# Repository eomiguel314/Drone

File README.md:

<img src="https://private-user-images.githubusercontent.com/155032115/534239275-43df6516-5e8d-49b2-8379-d691b3563eec.png?jwt=eyJ0eXAiOiJKV1QiLCJhbGciOiJIUzI1NiJ9.eyJpc3MiOiJnaXRodWIuY29tIiwiYXVkIjoicmF3LmdpdGh1YnVzZXJjb250ZW50LmNvbSIsImtleSI6ImtleTUiLCJleHAiOjE3NjgwNjI2MjAsIm5iZiI6MTc2ODA2MjMyMCwicGF0aCI6Ii8xNTUwMzIxMTUvNTM0MjM5Mjc1LTQzZGY2NTE2LTVlOGQtNDliMi04Mzc5LWQ2OTFiMzU2M2VlYy5wbmc_WC1BbXotQWxnb3JpdGhtPUFXUzQtSE1BQy1TSEEyNTYmWC1BbXotQ3JlZGVudGlhbD1BS0lBVkNPRFlMU0E1M1BRSzRaQSUyRjIwMjYwMTEwJTJGdXMtZWFzdC0xJTJGczMlMkZhd3M0X3JlcXVlc3QmWC1BbXotRGF0ZT0yMDI2MDExMFQxNjI1MjBaJlgtQW16LUV4cGlyZXM9MzAwJlgtQW16LVNpZ25hdHVyZT03NzFiOGY2MzdkZTdjZjNjMDJiNzgxZWViOGYxYjNmYWFjZmI5NjM2MTRmMWU0MmQyMjM3NjM1OWRiNDJlYmY5JlgtQW16LVNpZ25lZEhlYWRlcnM9aG9zdCJ9.WQfb5ywTV8FJy9Pylw90fT3kKYA23nSvT_et_dpvcMw"/>

# What is the project?
<p>This is a quadcopter with a flight controler based on esp32 with Mpu6050 and BME280....<p/>

# PCB of the flight controller

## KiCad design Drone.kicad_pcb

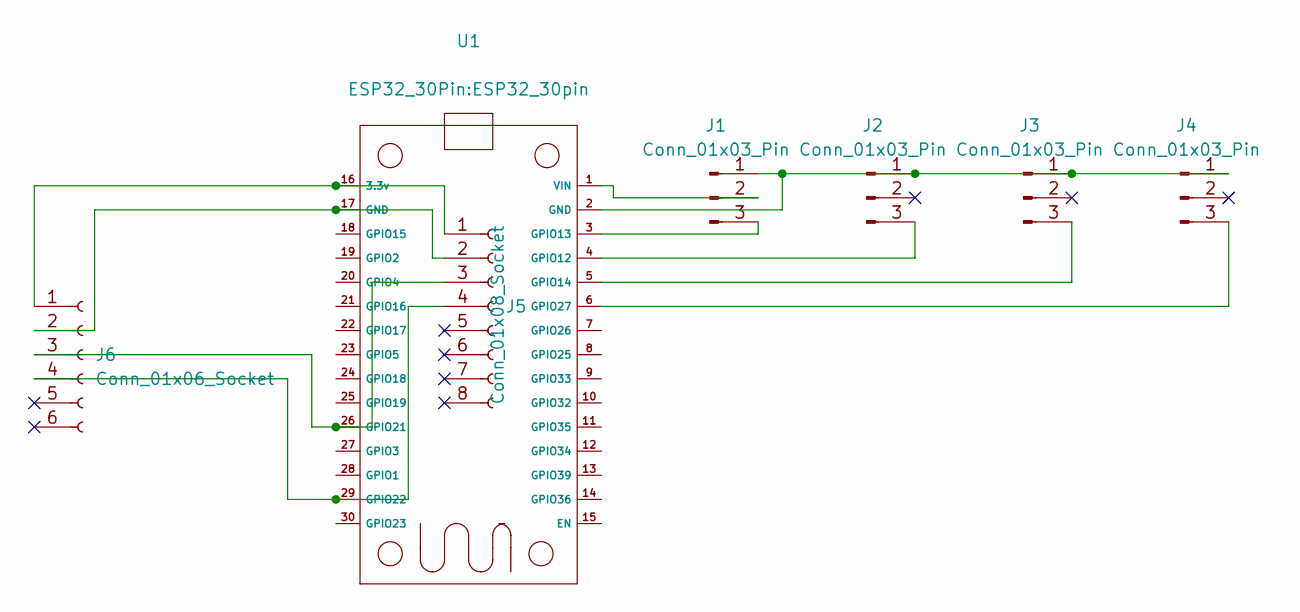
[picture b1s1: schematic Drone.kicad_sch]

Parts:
J1, J2, J3, J4: Conn_01x03_Pin; FanPinHeader_1x03_P2.54mm_Vertical
J5: Conn_01x08_Socket
J6: Conn_01x06_Socket; PinHeader_1x06_P2.54mm_Vertical
U1: ESP32_30pin

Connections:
unnamed: J1.1, J2.1, J3.1, J4.1, U1.2 (GND)
unnamed: J1.2, U1.1 (VIN)
unnamed: J1.3, U1.3 (GPIO13)
unnamed: J2.3, U1.4 (GPIO12)
unnamed: J3.3, U1.5 (GPIO14)
unnamed: J4.3, U1.6 (GPIO27)
unnamed: J5.1, J6.1, U1.16 (3.3v)
unnamed: J5.2, J6.2, U1.17 (GND)
unnamed: J5.3, J6.3, U1.26 (GPIO21)
unnamed: J5.4, J6.4, U1.29 (GPIO22)

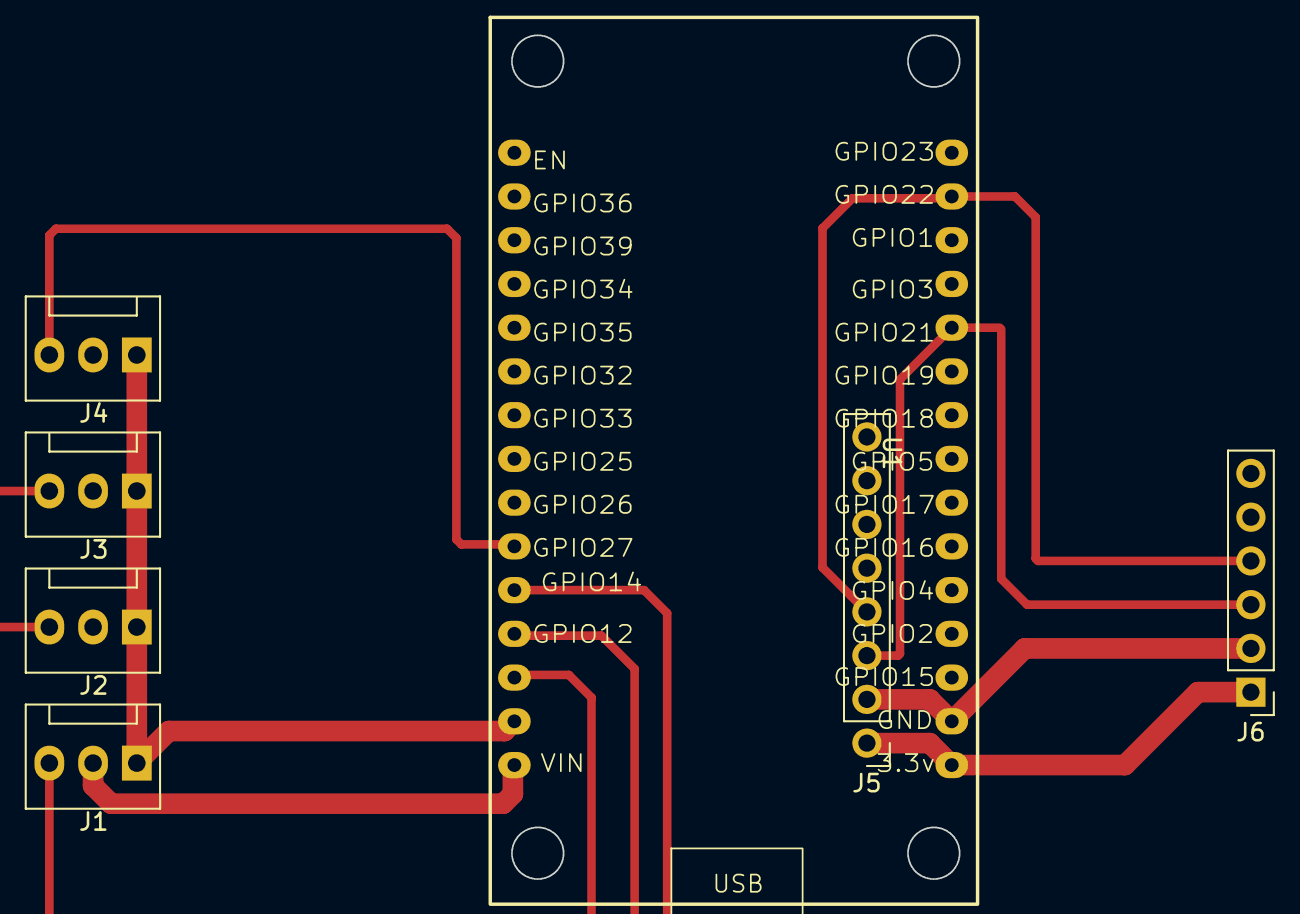
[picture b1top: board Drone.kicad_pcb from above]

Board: 2 copper layers, 7 parts (0 on the bottom side), 10 nets.

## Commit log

2025-11-06 Add web server control for brushless motor
    Implement a web server to control a brushless motor with ESP32. Includes HTML interface for turning the motor on and off.
2025-11-06 Rename index.ino to IoTInterface.ino
2026-01-08 Add Kalman filter implementation for MPU6050
2026-01-08 Fix typo in serial initialization loop
2026-01-10 Add image to README
2026-01-10 Update README with project info and image
    Added project description and image to README.
2026-01-13 Update README with project details and image
    Added image and updated project description.
2026-01-17 Add FlightController.cpp generated from Simulink model
2026-01-17 Add flightController header file with model definitions
2026-01-17 Fix header formatting for PCB section in README
2026-02-08 Add basic drone control with PID and sensors
2026-02-08 PCB FILES
